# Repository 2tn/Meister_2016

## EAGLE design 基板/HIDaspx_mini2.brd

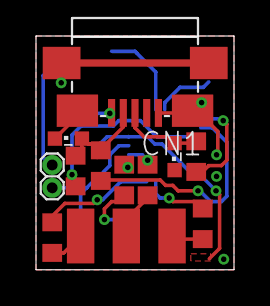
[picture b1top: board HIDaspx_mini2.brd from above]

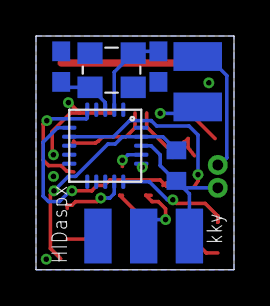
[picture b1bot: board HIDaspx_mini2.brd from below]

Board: 2 copper layers, 11.0 x 13.0 mm, 18 parts (6 on the bottom side), 20 nets.

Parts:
C4, C5: 22p; C0603
CN1: ZX62R-B-5P; MICRO-B
JP1: 1X02/HALF
LED1, LED2: BLUE; SML0603
PSW: 100m; C3225
R2: 2.2k; R0603
R3, R4: 75; R0603
R5: 10k; R0603
R6, R7, R8, R9: 100; R0603
U$1: TINY2313-*M*; MLF20
U$2: AVR-ISP-6-EDGE; 6PAD_ISP
X1: FA238V; V66RA

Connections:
GND: C4.2, C5.2, CN1.5, CN1.CASE@1, CN1.CASE@2, CN1.CASE@3, CN1.CASE@4, LED1.C, LED2.C, U$1.P$8, U$2.GND, X1.P2GND, X1.P4GND
MISO: R7.1, U$1.P$15
MOSI: R6.2, U$1.P$16
unnamed: C5.1, U$1.P$2, X1.P1X1
unnamed: JP1.2, PSW.1
unnamed: C4.1, U$1.P$3, X1.P3X2
unnamed: CN1.1, PSW.2
unnamed: CN1.2, LED2.A, R2.2, R3.2
unnamed: CN1.3, LED1.A, R4.2
unnamed: R2.1, U$1.P$7
unnamed: R3.1, U$1.P$6
unnamed: R4.1, U$1.P$5
unnamed: R5.2, U$1.P$19
unnamed: R8.2, U$2.SCK
unnamed: R7.2, U$2.MISO
unnamed: R9.2, U$2.RST
unnamed: R6.1, U$2.MOSI
RST: R9.1, U$1.P$14
SCK: R8.1, U$1.P$17
VCC: JP1.1, R5.1, U$1.P$18, U$2.VCC

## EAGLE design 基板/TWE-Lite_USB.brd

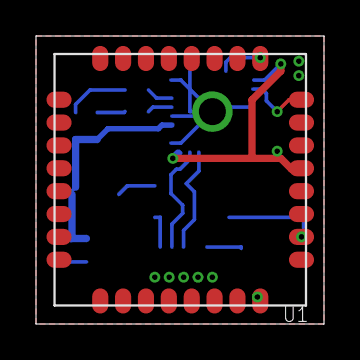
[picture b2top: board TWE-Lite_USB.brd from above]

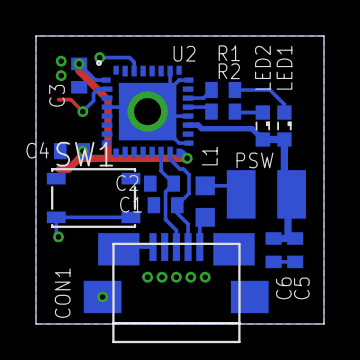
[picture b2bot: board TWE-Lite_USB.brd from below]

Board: 2 copper layers, 16.0 x 16.0 mm, 16 parts (15 on the bottom side), 14 nets.

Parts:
C1, C2, C3, C4, C5, C6: 0402
CON1: ZX62R-B-5P; MICRO-B
L1: C0603K
LED1, LED2: SML0603
PSW: 100m; C3225
R1, R2: R0402
SW1: SKRPACE010
U1: TWE-LITE_SMD; LITE
U2: FT232RQ; QFN32

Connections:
+3V3: C3.1, C4.1, U1.5, U2.1, U2.16
+5V: C5.1, C6.1, LED1.A, LED2.A, PSW.1, U2.19
GND: C1.2, C2.2, C3.2, C4.2, C5.2, C6.2, CON1.5, CON1.CASE@1, CON1.CASE@2, CON1.CASE@3, CON1.CASE@4, SW1.1, SW1.2, U1.20, U1.28, U1.30, U1.31, U1.32, U2.4, U2.17, U2.20, U2.24, U2.26, U2.PAD
unnamed: C1.1, CON1.2, U2.15
unnamed: C2.1, CON1.3, U2.14
unnamed: CON1.1, L1.2
unnamed: LED1.C, R1.2
unnamed: U1.9, U2.30
unnamed: U1.8, U2.2
unnamed: SW1.3, SW1.4, U1.2
unnamed: L1.1, PSW.2
unnamed: LED2.C, R2.2
unnamed: R1.1, U2.22
unnamed: R2.1, U2.21

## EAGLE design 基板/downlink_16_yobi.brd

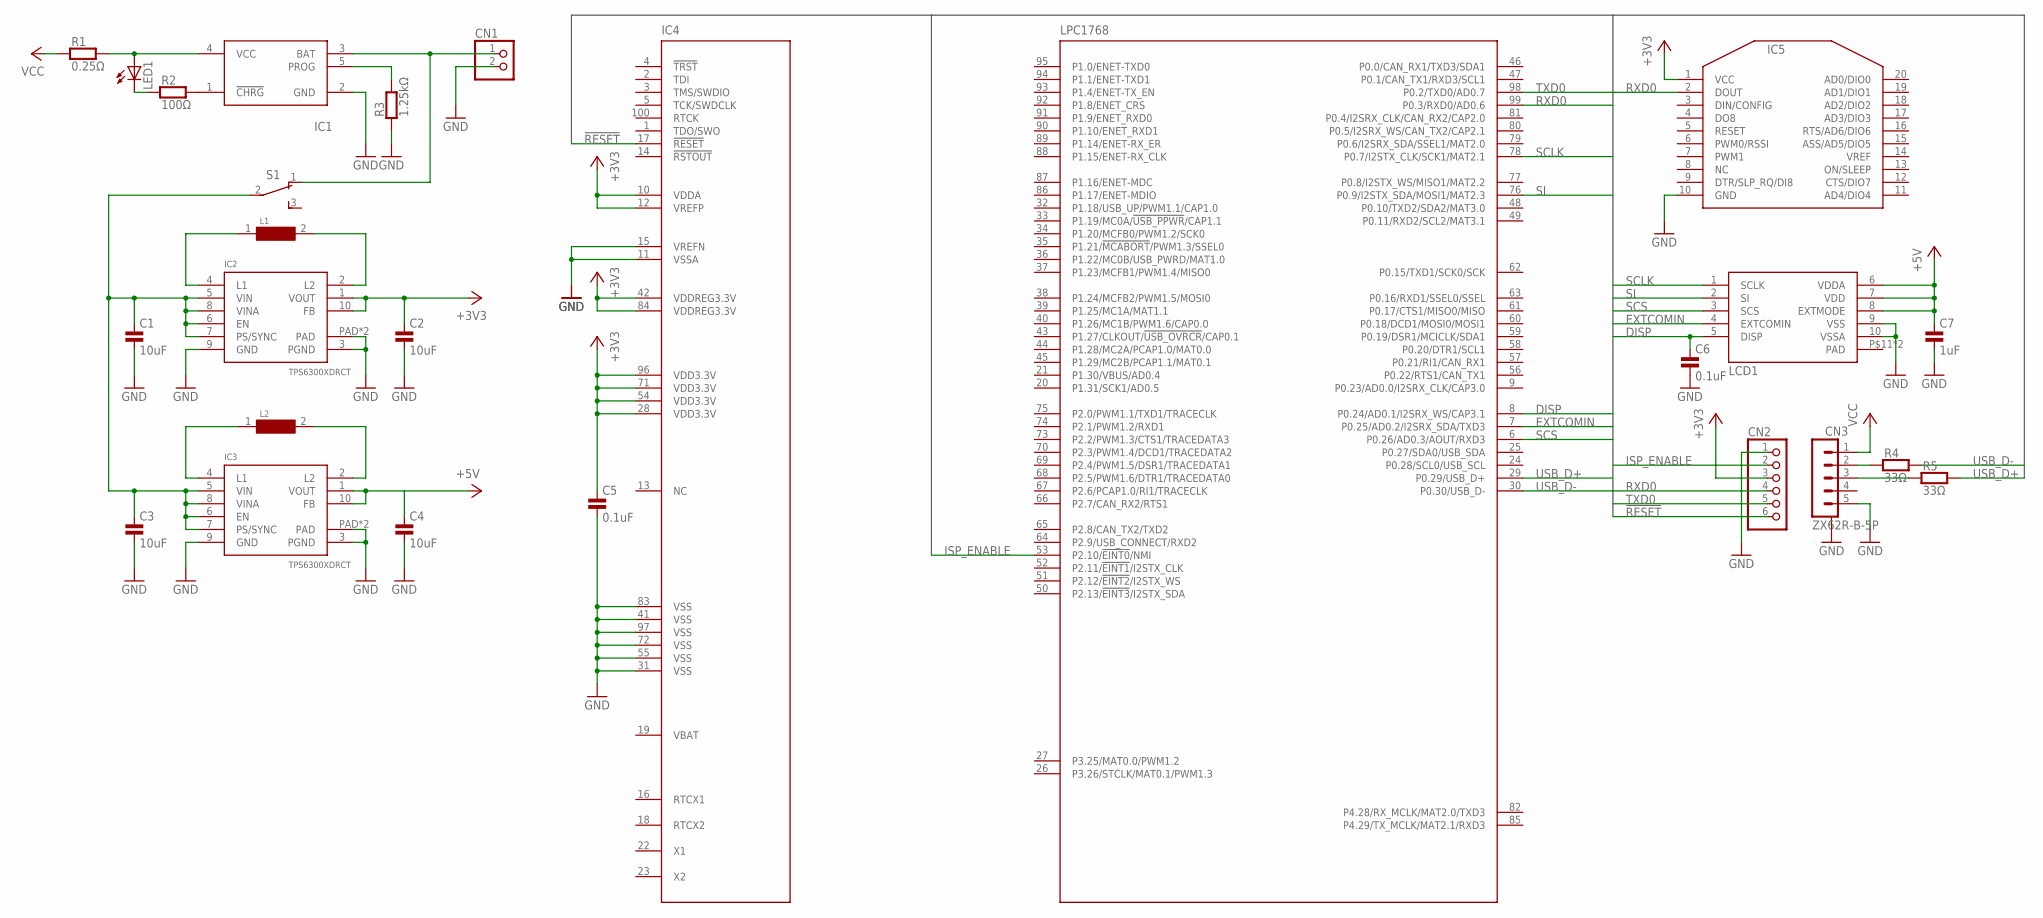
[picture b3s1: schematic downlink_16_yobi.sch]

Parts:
C1, C2, C3, C4: 10uF; 0603
C5, C6: 0.1uF; 0603
C7: 1uF; 0603
CN1: PINHD-1X2; 1X02
CN2: PINHD-1X6/90; 1X06/90
CN3: ZX62R-B-5P; MICRO-B
IC1: LTC4054; TSOT23-5
IC2, IC3: TPS6300XDRCT; S-PVSON-N10
IC4: LPC1768; LQFP100
IC5: XBEE-PRO2MM; XBEE-ZB
L1, L2: VLF4012ST
LCD1: LS027B4DH01SMD; FH12-10S-0.5SH
LED1: LEDSML0603; SML0603
R1: 0.25Ω; 0603
R2: 100Ω; 0603
R3: 1.25kΩ; 0603
R4, R5: 33Ω; 0603
S1: SS-12D00

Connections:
!RESET!: CN2.6, IC4.17 (!RESET!)
+3V3: C2.1, C5.1, CN2.3, IC2.1 (VOUT), IC2.10 (FB), IC4.10 (VDDA), IC4.12 (VREFP), IC4.28 (VDD3.3V), IC4.42 (VDDREG3.3V), IC4.54 (VDD3.3V), IC4.71 (VDD3.3V), IC4.84 (VDDREG3.3V), IC4.96 (VDD3.3V), IC5.1 (VCC)
+5V: C4.1, C7.1, IC3.1 (VOUT), IC3.10 (FB), LCD1.6 (VDDA), LCD1.7 (VDD), LCD1.8 (EXTMODE)
DISP: C6.1, IC4.8 (P0.24/AD0.1/I2SRX_WS/CAP3.1), LCD1.5 (DISP)
EXTCOMIN: IC4.7 (P0.25/AD0.2/I2SRX_SDA/TXD3), LCD1.4 (EXTCOMIN)
GND: C1.2, C2.2, C3.2, C4.2, C5.2, C6.2, C7.2, CN1.2, CN2.1, CN3.5 (1.VBUS), CN3.CASE@1, CN3.CASE@2, CN3.CASE@3, CN3.CASE@4, IC1.2 (GND), IC2.3 (PGND), IC2.9 (GND), IC2.PAD, IC2.PAD@1 (PAD), IC3.3 (PGND), IC3.9 (GND), IC3.PAD, IC3.PAD@1 (PAD), IC4.11 (VSSA), IC4.15 (VREFN), IC4.31 (VSS), IC4.41 (VSS), IC4.55 (VSS), IC4.72 (VSS), IC4.83 (VSS), IC4.97 (VSS), IC5.10 (GND), LCD1.9 (VSS), LCD1.10 (VSSA), R3.1
ISP_ENABLE: CN2.2, IC4.53 (P2.10/!EINT0!/NMI)
unnamed: CN3.2 (4.ID), R4.1
unnamed: CN3.3 (3.D+), R5.1
unnamed: IC1.5 (PROG), R3.2
unnamed: IC1.4 (VCC), LED1.A, R1.2
unnamed: CN1.1, IC1.3 (BAT), S1.1 (O)
unnamed: IC1.1 (!CHRG!), R2.2
unnamed: LED1.C, R2.1
unnamed: IC2.4 (L1), L1.1
unnamed: IC2.2 (L2), L1.2
unnamed: IC3.4 (L1), L2.1
unnamed: IC3.2 (L2), L2.2
unnamed: C1.1, C3.1, IC2.5 (VIN), IC2.6 (EN), IC2.7 (PS/SYNC), IC2.8 (VINA), IC3.5 (VIN), IC3.6 (EN), IC3.7 (PS/SYNC), IC3.8 (VINA), S1.2
RXD0: CN2.4, IC4.99 (P0.3/RXD0/AD0.6), IC5.2 (DOUT)
SCLK: IC4.78 (P0.7/I2STX_CLK/SCK1/MAT2.1), LCD1.1 (SCLK)
SCS: IC4.6 (P0.26/AD0.3/AOUT/RXD3), LCD1.3 (SCS)
SI: IC4.76 (P0.9/I2STX_SDA/MOSI1/MAT2.3), LCD1.2 (SI)
TXD0: CN2.5, IC4.98 (P0.2/TXD0/AD0.7)
USB_D+: IC4.29 (P0.29/USB_D+), R5.2
USB_D-: IC4.30 (P0.30/USB_D-), R4.2
VCC: CN3.1 (5.GND), R1.1

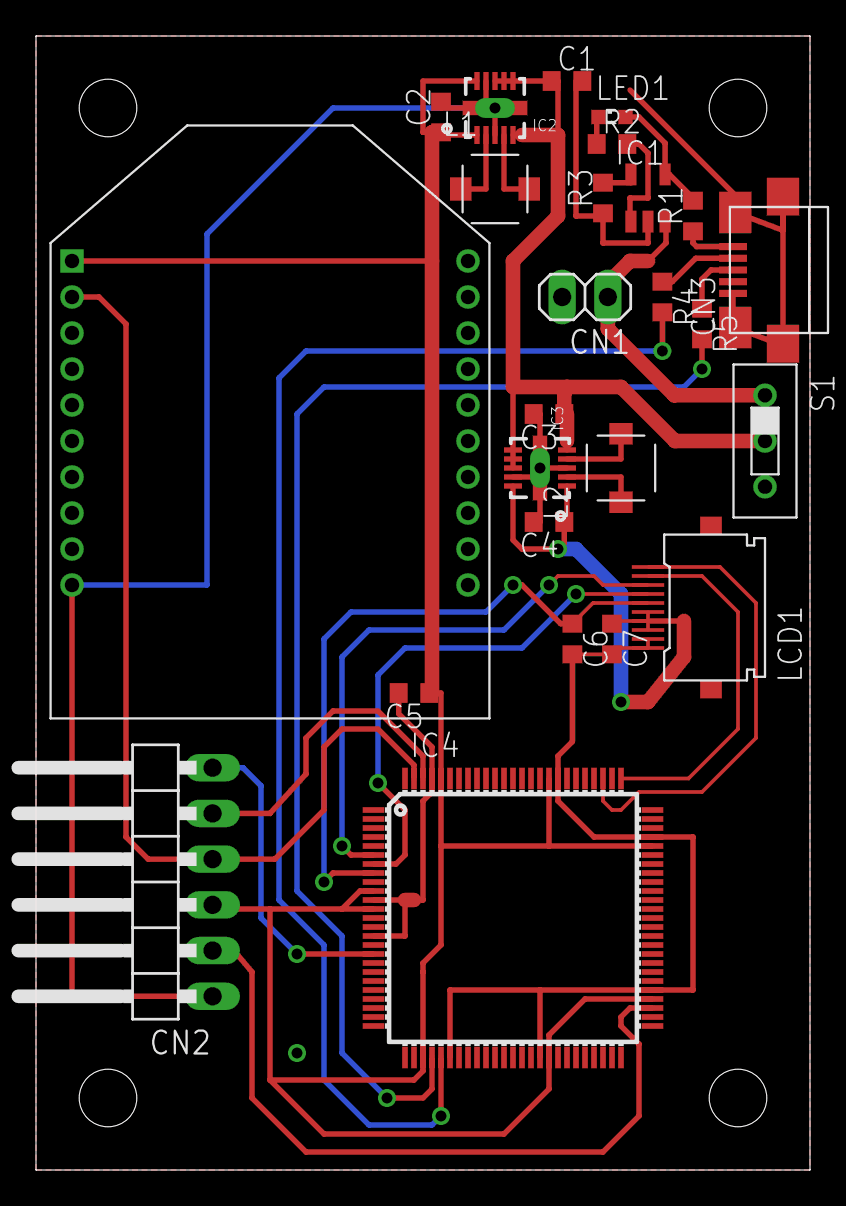
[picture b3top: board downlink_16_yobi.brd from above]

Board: 2 copper layers, 43.0 x 63.0 mm, 25 parts (0 on the bottom side), 27 nets.

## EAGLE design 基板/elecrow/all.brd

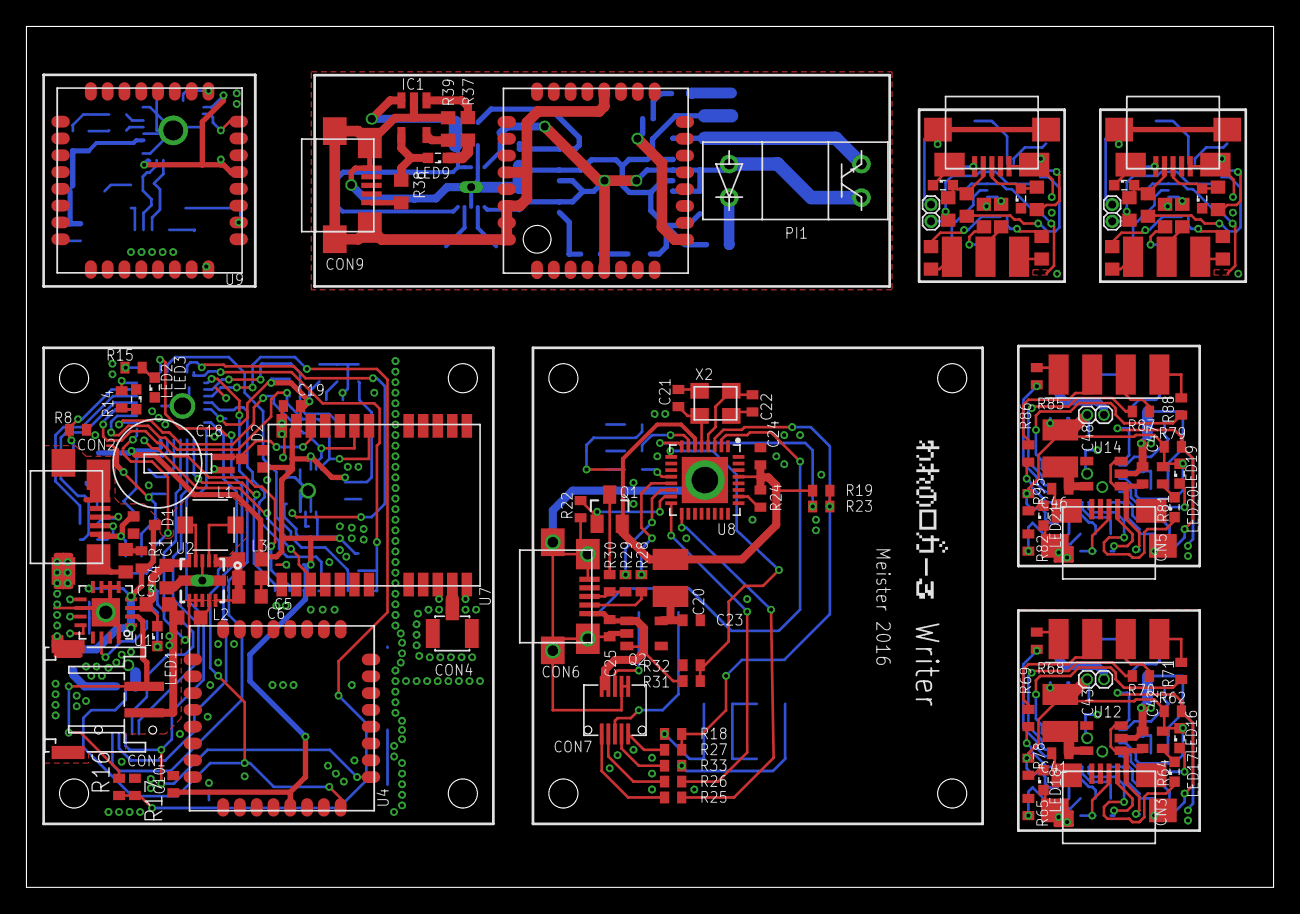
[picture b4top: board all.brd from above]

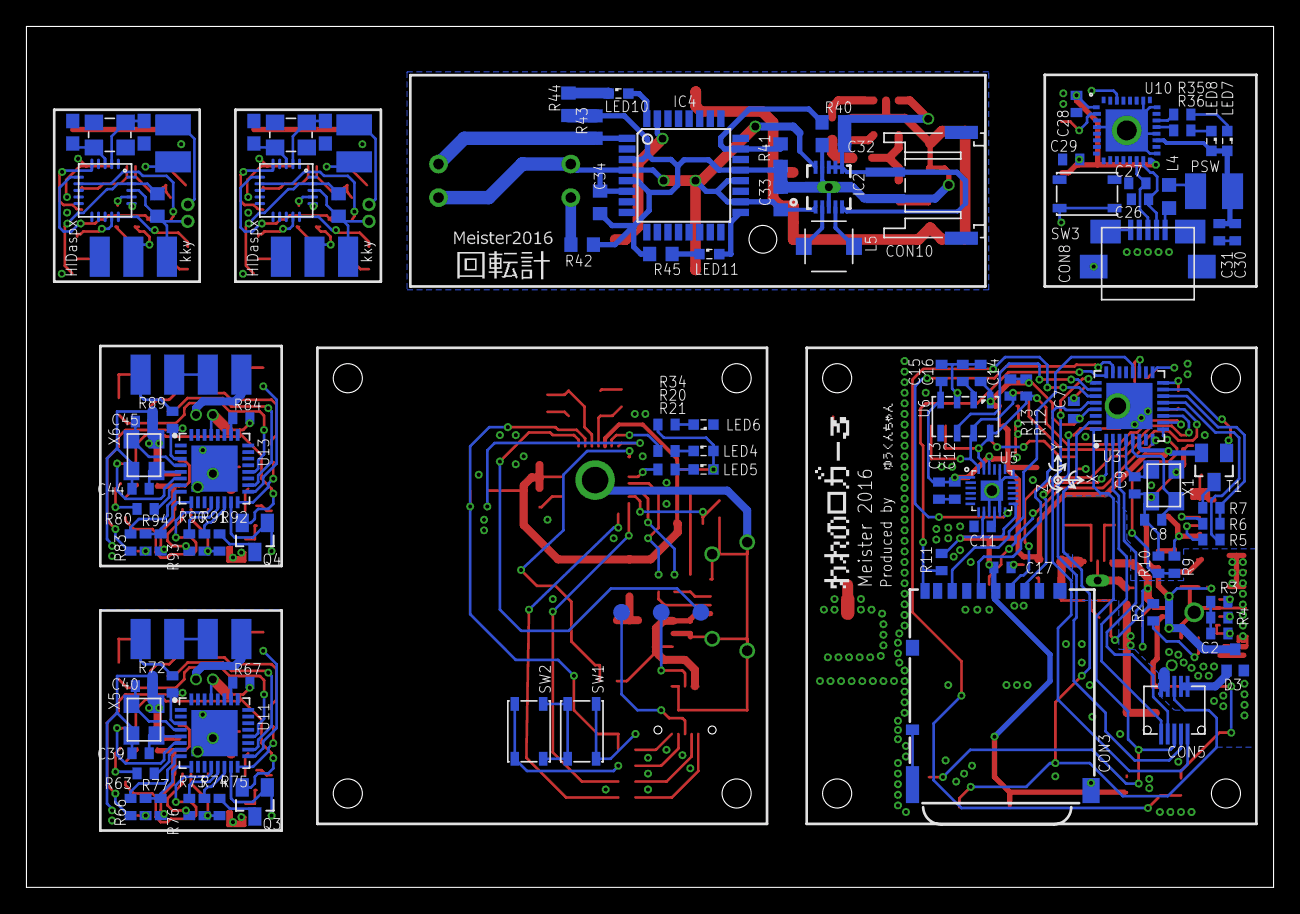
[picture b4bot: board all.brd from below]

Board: 2 copper layers, 94.3 x 65.1 mm, 236 parts (113 on the bottom side), 217 nets.

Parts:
C1, C3, C4, C5, C6, C32, C33: 10u; 0603
C2: 0.2u; 0402
C7, C10, C11, C12, C14, C16, C17, C19: 0.1u; 0402
C8, C9, C26, C27, C28, C29, C30, C31: 0402
C13: 10n; 0402
C15: 10u; 0402
C18: DCK-3R3E224-E
C20, C43, C48: PSW; C3225
C21, C22, C39, C40, C44, C45: 8P; C0402
C23, C25, C41, C42, C46, C47: 1u; C0402
C24: 0.1u; C0402
C34: 0.1u; 0603
C35, C36, C37, C38: 22p; C0603
CN1, CN2, CN3, CN5: ZX62R-B-5P; MICRO-B
CN4, CN6: 2X4SMD
CON1, CON10: JST-PH2
CON2, CON6, CON8, CON9: ZX62R-B-5P; MICRO-B
CON3: DM3AT-SF-PEJM5SMD; DM3AT-SF-PEJM5
CON4: U.FL; U.FL-R-SMT-1
CON5: DF12#-10DS; DF12A-10DS
CON7: DF12#-10DP; DF12D-10DP
D1, D2, D3: RB461F; UMD3
IC1: TSOT23-5
IC2: S-PVSON-N10
IC3: LITESMD; LITE
IC4: ATMEGA48/88/168-AU; TQFP32-08
JP1, JP2: 1X02/HALF
JP3, JP4: 1X02/HARF
L1, L5: 2.2u; VLF4012ST
L2, L3: BLM; C0603K
L4: C0603K
LED1, LED2, LED3, LED4, LED5, LED6, LED7, LED8, LED9, LED10, LED11, LED16, LED17, LED18, LED19, LED20, LED21: SML0603
LED12, LED13, LED14, LED15: BLUE; SML0603
PI1: RPI-574
PSW, PSW1, PSW2: 100m; C3225
Q1, Q3, Q4: PDTA114ET; SOT23
Q2: MIC550X; SOT23_5PIN
R1: 1; 0402
R2, R14, R15: 100; 0402
R3: 105k; 0402
R4: 124k; 0402
R5, R6: 33; 0402
R7: 1.5k; 0402
R8, R10: 10k; 0402
R9: 5.6k; 0402
R11, R12, R13: 4.7k; 0402
R16: 3.3k; 0402
R17: 2.2k; 0402
R18, R23, R25, R26, R27, R33, R66, R68, R69, R70, R71, R72, R83, R85, R86, R87, R88, R89: 270; R0402
R19, R22, R24, R32, R62, R65, R67, R77, R79, R82, R84, R94: 10k; R0402
R20, R21, R30, R63, R64, R75, R80, R81, R92: 1.5k; R0402
R28, R29, R73, R74, R90, R91: 33; R0402
R31, R76, R93: 5.6k; R0402
R34, R78, R95: 750; R0402
R35, R36: R0402
R37: 100; 0603
R38: 0.25; 0603
R39: 3.2k; 0603
R40: 3.3k; 0603
R41: 2.2k; 0603
R42, R44, R45: 200; 0603
R43: 1.0M; 0603
R46, R54: 2.2k; R0603
R47, R48, R55, R56: 75; R0603
R49, R57: 10k; R0603
R50, R51, R52, R53, R58, R59, R60, R61: 100; R0603
SW1, SW2, SW3: SKRPACE010
T1: PDTA114ET; SOT23
U1: LTC4055; QFN16
U2: TPS6300XDRCT; S-PVSON-N10
U3, U8, U11, U13: LPC11U35FHI33/501; SOT617-3
U4, U9: TWE-LITE_SMD; LITE
U5: MPU-9250
U6: MPL3115A2
U7: NEO-7M
U10: FT232RQ; QFN32
U12, U14: MIC550X; SOT23_5PIN
U$1: DIRECTION
U$2, U$3, U$4: TESTPAD
U$5, U$7: TINY2313-*M*; MLF20
U$6, U$8: AVR-ISP-6-EDGE; 6PAD_ISP
X1, X2, X3, X4, X5, X6: FA238V; V66RA

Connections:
!RESET!: CON5.10, U3.2
!USB_CONNECT!: R8.2, T1.1, U3.15
!USB_CONNECT!1: Q1.1, R22.2, U8.15
!USB_CONNECT!2: Q3.1, R65.2, U11.15
!USB_CONNECT!3: Q4.1, R82.2, U13.15
+3V1: C28.1, C29.1, U9.5, U10.1, U10.16
+3V2: C33.1, C34.1, IC2.1, IC2.10, IC3.5, IC4.4, IC4.6, IC4.18, IC4.20, PI1.DA, PI1.TC
+3V3: C7.1, C10.1, C12.1, C13.1, C14.1, C15.1, C17.1, C19.1, CON3.4, D2.2, L3.1, R11.2, R12.2, R13.2, T1.2, U3.6, U3.29, U4.5, U5.1, U5.8, U5.13, U5.22, U6.1, U6.4, U7.23
+5V: D1.3, D3.3, R1.2, U1.1, U1.4, U1.8
+5V1: C30.1, C31.1, LED7.A, LED8.A, PSW.1, U10.19
AD7: R16.1, R17.2, U3.27
BOOT: CON7.8, R33.2
D+USB: CON6.3, R29.2, R30.1
D+USB1: CN3.3, R74.2, R75.1
D+USB2: CN5.3, R91.2, R92.1
D-USB: CON6.2, R28.2
D-USB1: CN3.2, R73.2
D-USB2: CN5.2, R90.2
GND: C5.2, C6.2, C7.2, C8.2, C9.2, C10.2, C11.2, C12.2, C13.2, C14.2, C15.2, C16.2, C17.2, C18.1, C19.2, CON3.6, CON3.10, CON3.P$10, CON3.P$11, CON3.P$12, CON3.P$14, CON4.1, CON4.2, L2.2, LED2.C, LED3.C, R8.1, R10.1, R17.1, U2.9, U3.33, U4.20, U4.28, U4.30, U4.31, U4.32, U5.9, U5.11, U5.18, U5.20, U5.PAD, U6.3, U7.10, U7.12, U7.13, U7.24, X1.P2GND, X1.P4GND
GND1: C21.2, C22.2, C23.2, C24.2, C25.2, CON6.5, CON6.CASE@1, CON6.CASE@2, CON6.CASE@3, CON6.CASE@4, CON7.7, CON7.9, LED6.C, Q2.2, R22.1, R32.1, SW1.1, SW1.2, SW2.1, SW2.2, U8.33, X2.P2GND, X2.P4GND
GND2: C26.2, C27.2, C28.2, C29.2, C30.2, C31.2, CON8.5, CON8.CASE@1, CON8.CASE@2, CON8.CASE@3, CON8.CASE@4, SW3.1, SW3.2, U9.20, U9.28, U9.30, U9.31, U9.32, U10.4, U10.17, U10.20, U10.24, U10.26, U10.PAD
GND3: C32.2, C33.2, C34.2, CON9.5, CON9.CASE@1, CON9.CASE@2, CON9.CASE@3, CON9.CASE@4, CON10.1, IC1.2, IC2.3, IC2.9, IC2.PAD, IC2.PAD@1, IC3.20, IC3.28, IC3.30, IC3.31, IC3.32, IC4.3, IC4.5, IC4.21, R39.1, R41.1, R42.1, R43.2, R44.1, R45.1
GND4: C35.2, C36.2, CN1.5, CN1.CASE@1, CN1.CASE@2, CN1.CASE@3, CN1.CASE@4, LED12.C, LED13.C, U$5.P$8, U$6.GND, X3.P2GND, X3.P4GND
GND5: C37.2, C38.2, CN2.5, CN2.CASE@1, CN2.CASE@2, CN2.CASE@3, CN2.CASE@4, LED14.C, LED15.C, U$7.P$8, U$8.GND, X4.P2GND, X4.P4GND
GND6: C39.2, C40.2, C41.2, C42.2, CN3.5, CN3.CASE@1, CN3.CASE@2, CN3.CASE@3, CN3.CASE@4, CN4.3, CN4.5, LED18.C, R65.1, R77.1, U11.33, U12.2, X5.P2GND, X5.P4GND
GND7: C44.2, C45.2, C46.2, C47.2, CN5.5, CN5.CASE@1, CN5.CASE@2, CN5.CASE@3, CN5.CASE@4, CN6.3, CN6.5, LED21.C, R82.1, R94.1, U13.33, U14.2, X6.P2GND, X6.P4GND
MISO1: CON3.7, U3.20
MISO2: R59.1, U$7.P$15
MISO3: R51.1, U$5.P$15
MOSI1: CON3.3, U3.12
MOSI2: R58.2, U$7.P$16
MOSI3: R50.2, U$5.P$16
unnamed: C8.1, U3.5, X1.P1X1
unnamed: CON2.2, R5.1
unnamed: C9.1, U3.4, X1.P3X2
unnamed: CON2.3, R6.1
unnamed: R7.2, T1.3
unnamed: LED3.A, R15.1
unnamed: CON4.3, U7.11
unnamed: C16.1, U6.2
unnamed: L1.2, U2.2
unnamed: C11.1, U5.10
unnamed: L1.1, U2.4
unnamed: LED2.A, R14.1
unnamed: C21.1, U8.5, X2.P1X1
unnamed: C22.1, U8.4, X2.P3X2
unnamed: R29.1, U8.14
unnamed: C1.1, R1.1
unnamed: C5.1, C6.1, L3.2, U2.1, U2.10
unnamed: CON5.1, CON5.3, D3.2
unnamed: R3.2, U1.9
unnamed: R4.2, U1.11
unnamed: C2.1, U1.12
unnamed: R2.1, U1.14
unnamed: LED1.C, R2.2
unnamed: C3.1, C4.1, LED1.A, U1.3, U2.5, U2.6, U2.7, U2.8
unnamed: CON1.1, R16.2, U1.2
unnamed: C18.2, D2.3, U7.22
unnamed: R28.1, U8.13
unnamed: Q1.3, R30.2
unnamed: CON7.2, R25.1
unnamed: CON7.4, R26.1
unnamed: LED6.A, R34.2
unnamed: LED4.C, R20.1
unnamed: C20.2, C23.1, Q2.5
unnamed: CON7.10, R27.1
unnamed: R18.1, SW1.3, SW1.4
unnamed: R33.1, SW2.3, SW2.4
unnamed: U8.2, U$4.P$1
unnamed: LED5.C, R21.1
unnamed: C26.1, CON8.2, U10.15
unnamed: C27.1, CON8.3, U10.14
unnamed: CON8.1, L4.2
unnamed: U9.9, U10.30
unnamed: U9.8, U10.2
unnamed: L4.1, PSW.2
unnamed: LED7.C, R35.2
unnamed: LED8.C, R36.2
unnamed: R35.1, U10.22
unnamed: R36.1, U10.21
unnamed: SW3.3, SW3.4, U9.2
unnamed: IC1.4, LED9.A, R38.2
unnamed: IC1.1, R37.2
unnamed: LED9.C, R37.1
unnamed: IC2.4, L5.1
unnamed: IC2.2, L5.2
unnamed: CON9.1, R38.1
unnamed: IC1.5, R39.2
unnamed: IC4.23, R40.1, R41.2
unnamed: IC4.1, PI1.TE, R43.1
unnamed: PI1.DC, R42.2
unnamed: IC4.17, LED11.A
unnamed: LED11.C, R45.2
unnamed: IC4.32, LED10.A
unnamed: LED10.C, R44.2
unnamed: C36.1, U$5.P$2, X3.P1X1
unnamed: C35.1, U$5.P$3, X3.P3X2
unnamed: CN1.1, PSW1.2
unnamed: CN1.2, LED13.A, R46.2, R47.2
unnamed: CN1.3, LED12.A, R48.2
unnamed: R46.1, U$5.P$7
unnamed: R47.1, U$5.P$6
unnamed: R48.1, U$5.P$5
unnamed: R49.2, U$5.P$19
unnamed: R52.2, U$6.SCK
unnamed: R51.2, U$6.MISO
unnamed: R53.2, U$6.RST
unnamed: R50.1, U$6.MOSI
unnamed: JP1.2, PSW1.1
unnamed: C38.1, U$7.P$2, X4.P1X1
unnamed: C37.1, U$7.P$3, X4.P3X2
unnamed: CN2.1, PSW2.2
unnamed: CN2.2, LED15.A, R54.2, R55.2
unnamed: CN2.3, LED14.A, R56.2
unnamed: R54.1, U$7.P$7
unnamed: R55.1, U$7.P$6
unnamed: R56.1, U$7.P$5
unnamed: R57.2, U$7.P$19
unnamed: R60.2, U$8.SCK
unnamed: R59.2, U$8.MISO
unnamed: R61.2, U$8.RST
unnamed: R58.1, U$8.MOSI
unnamed: JP2.2, PSW2.1
unnamed: C39.1, U11.5, X5.P1X1
unnamed: C40.1, U11.4, X5.P3X2
unnamed: R74.1, U11.14
unnamed: R73.1, U11.13
unnamed: Q3.3, R75.2
unnamed: CN4.2, R68.1
unnamed: CN4.4, R69.1
unnamed: CN4.6, R70.1
unnamed: CN4.8, R71.1
unnamed: LED18.A, R78.2
unnamed: LED17.A, R64.2
unnamed: LED16.C, R63.1
unnamed: C41.1, C43.2, U12.5
unnamed: CN4.7, R72.1
unnamed: CN4.1, JP3.1
unnamed: C44.1, U13.5, X6.P1X1
unnamed: C45.1, U13.4, X6.P3X2
unnamed: R91.1, U13.14
unnamed: R90.1, U13.13
unnamed: Q4.3, R92.2
unnamed: CN6.2, R85.1
unnamed: CN6.4, R86.1
unnamed: CN6.6, R87.1
unnamed: CN6.8, R88.1
unnamed: LED21.A, R95.2
unnamed: LED20.A, R81.2
unnamed: LED19.C, R80.1
unnamed: C46.1, C48.2, U14.5
unnamed: CN6.7, R89.1
unnamed: CN6.1, JP4.1
PGND: C1.2, C2.2, C3.2, C4.2, CON1.2, CON1.PAD1, CON1.PAD2, CON2.5, CON2.CASE@1, CON2.CASE@2, CON2.CASE@3, CON2.CASE@4, CON5.7, CON5.9, L2.1, R3.1, R4.1, U1.5, U1.6, U1.7, U1.10, U1.16, U1.PAD, U2.3, U2.PAD, U2.PAD@1
PIO0_1: CON5.8, U3.3
PIO0_2: U3.8, U7.3
PIO0_3: R23.2, U8.8
PIO0_4: R24.1, U8.26
PIO0_5: R66.2, U11.8
PIO0_6: LED17.C, U11.12
PIO0_7: R14.2, U3.16
PIO0_8: R15.2, U3.17
PIO0_9: R67.1, U11.26
PIO0_10: R63.2, U11.7
PIO0_11: R83.2, U13.8
PIO0_12: LED20.C, U13.12
PIO0_13: U3.23, U5.12
PIO0_14: CON3.9, R11.1, U3.24
PIO0_15: R84.1, U13.26
PIO0_16: U3.26, U6.6
PIO0_17: R80.2, U13.7
PIO0_20: R20.2, U8.7
PIO0_21: R21.2, U8.12
PIO1_19: CON3.2, U3.1
RST1: R61.1, U$7.P$14
RST2: R53.1, U$5.P$14
RXD: CON5.5, U3.31, U4.8
RXD1: CON7.5, U$3.P$1
SCK1: CON3.5, U3.28
SCK2: R60.1, U$7.P$17
SCK3: R52.1, U$5.P$17
SCL: R12.1, U3.10, U5.23, U6.8, U7.19
SDA: R13.1, U3.11, U5.24, U6.7, U7.18
SWCLK: CON5.4, U3.19
SWDIO: CON5.2, U3.25
TARGET_!RESET!: R18.2, R19.2, R23.1, R27.2, U8.3
TARGET_!RESET!1: R62.2, R66.1, R72.2, U11.3
TARGET_!RESET!2: R79.2, R83.1, R89.2, U13.3
TARGET_SWCLK: R26.2, U8.16
TARGET_SWCLK1: R69.2, U11.16
TARGET_SWCLK2: R86.2, U13.16
TARGET_SWDIO: R25.2, U8.17
TARGET_SWDIO1: R68.2, U11.17
TARGET_SWDIO2: R85.2, U13.17
TARGET_SWO: R70.2, U11.18
TARGET_SWO1: R87.2, U13.18
TARGET_TDI: R71.2, U11.20
TARGET_TDI1: R88.2, U13.20
TXD: CON5.6, U3.32, U4.9
TXD1: CON7.6, U$2.P$1
U3: IC3.9, IC4.31
USB_D+: R6.2, R7.1, U3.14
USB_D-: R5.2, U3.13
USB_VBUS: R9.1, R10.2, U3.9
USB_VBUS1: R31.1, R32.2, U8.9
USB_VBUS2: R76.1, R77.2, U11.9
USB_VBUS3: R93.1, R94.2, U13.9
VBUS: CON2.1, D1.2, R9.2
VCC: C25.1, CON6.1, CON7.1, CON7.3, Q2.1, Q2.3, R31.2
VCC1: C32.1, CON10.2, IC1.3, IC2.5, IC2.6, IC2.7, IC2.8, R40.2
VCC2: JP1.1, R49.1, U$5.P$18, U$6.VCC
VCC3: JP2.1, R57.1, U$7.P$18, U$8.VCC
VCC4: C42.1, CN3.1, R76.2, U12.1, U12.3
VCC5: C47.1, CN5.1, R93.2, U14.1, U14.3
VDD: C20.1, C24.1, LED4.A, LED5.A, Q1.2, R19.1, R24.2, R34.1, U8.6, U8.29
VDD1: C43.1, JP3.2, LED16.A, Q3.2, R62.1, R64.1, R67.2, R78.1, U11.6, U11.29
VDD2: C48.1, JP4.2, LED19.A, Q4.2, R79.1, R81.1, R84.2, R95.1, U13.6, U13.29

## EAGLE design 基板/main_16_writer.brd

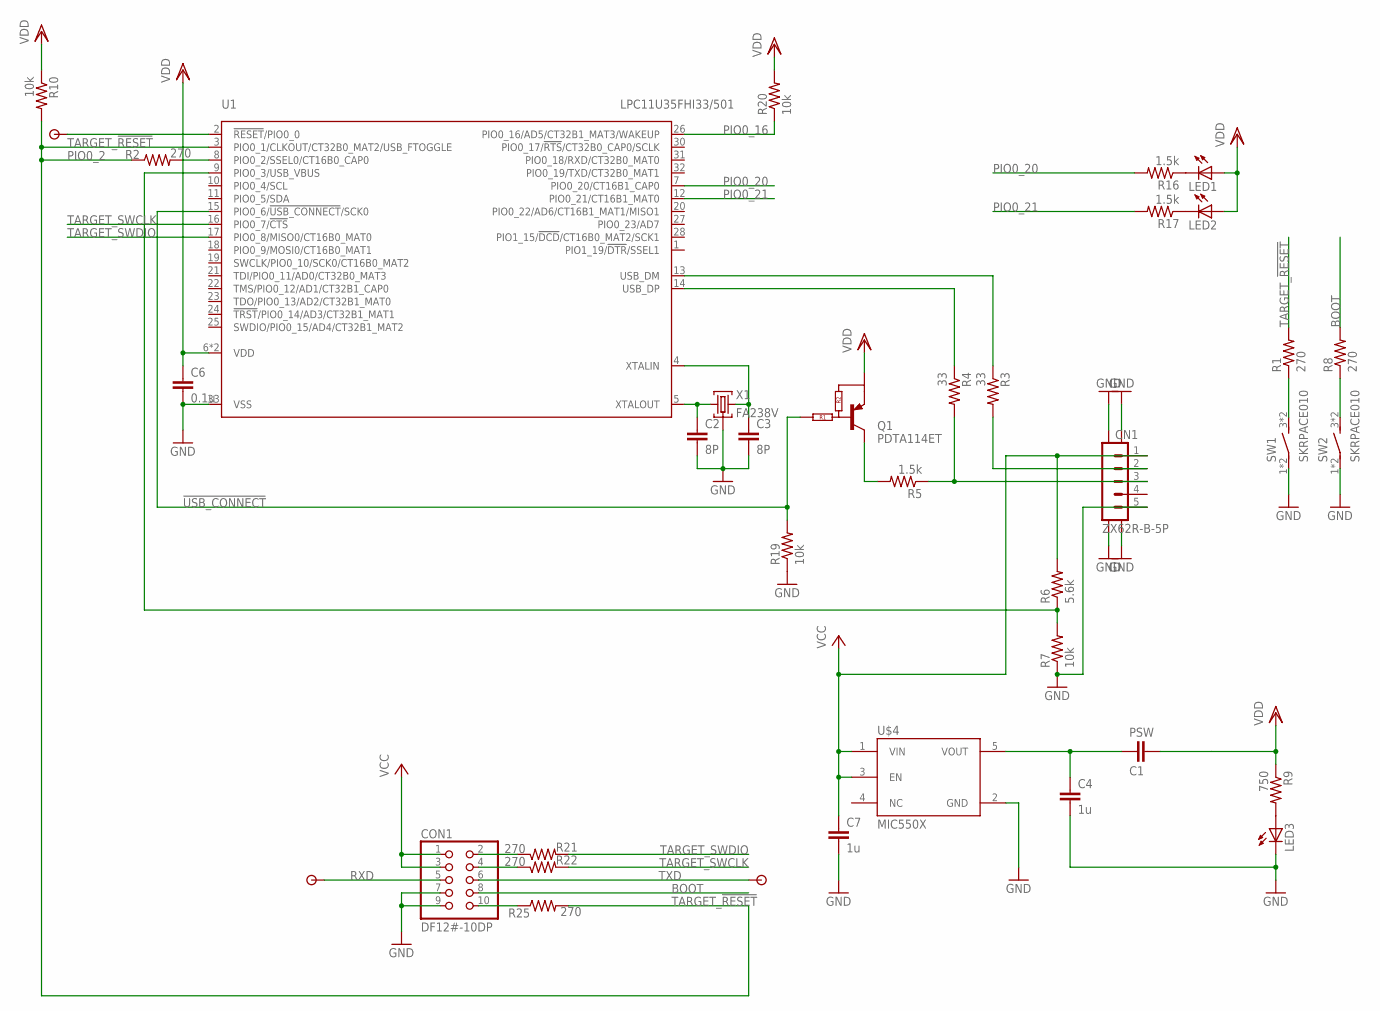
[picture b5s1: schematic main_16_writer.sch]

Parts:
C1: PSW; C3225
C2, C3: 8P; C0402
C4, C7: 1u; C0402
C6: 0.1u; C0402
CN1: ZX62R-B-5P; MICRO-B
CON1: DF12#-10DP; DF12D-10DP
LED1, LED2, LED3: LEDSML0603; SML0603
Q1: PDTA114ET; SOT23
R1, R2, R8, R21, R22, R25: 270; R0402
R3, R4: 33; R0402
R5, R16, R17: 1.5k; R0402
R6: 5.6k; R0402
R7, R10, R19, R20: 10k; R0402
R9: 750; R0402
SW1, SW2: SKRPACE010
U1: LPC11U35FHI33/501; SOT617-3
U$1, U$2, U$3: TESTPAD
U$4: MIC550X; SOT23_5PIN
X1: FA238V; V66RA

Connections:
!USB_CONNECT!: Q1.1 (INPUT), R19.2, U1.15 (PIO0_6/!USB_CONNECT!/SCK0)
BOOT: CON1.8, R8.2
D+USB: CN1.3 (3.D+), R4.2, R5.1
D-USB: CN1.2 (4.ID), R3.2
GND: C2.2, C3.2, C4.2, C6.2, C7.2, CN1.5 (1.VBUS), CN1.CASE@1 (1), CN1.CASE@2 (2), CN1.CASE@3 (3), CN1.CASE@4 (4), CON1.7, CON1.9, LED3.C, R7.1, R19.1, SW1.1, SW1.2, SW2.1, SW2.2, U1.33 (VSS), U$4.2 (GND), X1.P2GND (GND), X1.P4GND (GND)
unnamed: LED1.C, R16.1
unnamed: C2.1, U1.5 (XTALOUT), X1.P1X1 (X1)
unnamed: C3.1, U1.4 (XTALIN), X1.P3X2 (X2)
unnamed: C1.2, C4.1, U$4.5 (VOUT)
unnamed: R1.1, SW1.3 (S), SW1.4 (S)
unnamed: Q1.3 (C), R5.2
unnamed: R4.1, U1.14 (USB_DP)
unnamed: R3.1, U1.13 (USB_DM)
unnamed: CON1.10, R25.1
unnamed: LED2.C, R17.1
unnamed: R8.1, SW2.3 (S), SW2.4 (S)
unnamed: U1.2 (!RESET!/PIO0_0), U$3.P$1
unnamed: CON1.2, R21.1
unnamed: CON1.4, R22.1
unnamed: LED3.A, R9.2
PIO0_2: R2.2, U1.8 (PIO0_2/SSEL0/CT16B0_CAP0)
PIO0_16: R20.1, U1.26 (PIO0_16/AD5/CT32B1_MAT3/WAKEUP)
PIO0_20: R16.2, U1.7 (PIO0_20/CT16B1_CAP0)
PIO0_21: R17.2, U1.12 (PIO0_21/CT16B1_MAT0)
RXD: CON1.5, U$2.P$1
TARGET_!RESET!: R1.2, R2.1, R10.2, R25.2, U1.3 (PIO0_1/CLKOUT/CT32B0_MAT2/USB_FTOGGLE)
TARGET_SWCLK: R22.2, U1.16 (PIO0_7/!CTS!)
TARGET_SWDIO: R21.2, U1.17 (PIO0_8/MISO0/CT16B0_MAT0)
TXD: CON1.6, U$1.P$1
USB_VBUS: R6.1, R7.2, U1.9 (PIO0_3/USB_VBUS)
VCC: C7.1, CN1.1 (5.GND), CON1.1, CON1.3, R6.2, U$4.1 (VIN), U$4.3 (EN)
VDD: C1.1, C6.1, LED1.A, LED2.A, Q1.2 (E), R9.1, R10.1, R20.2, U1.6 (VDD), U1.29 (VDD)

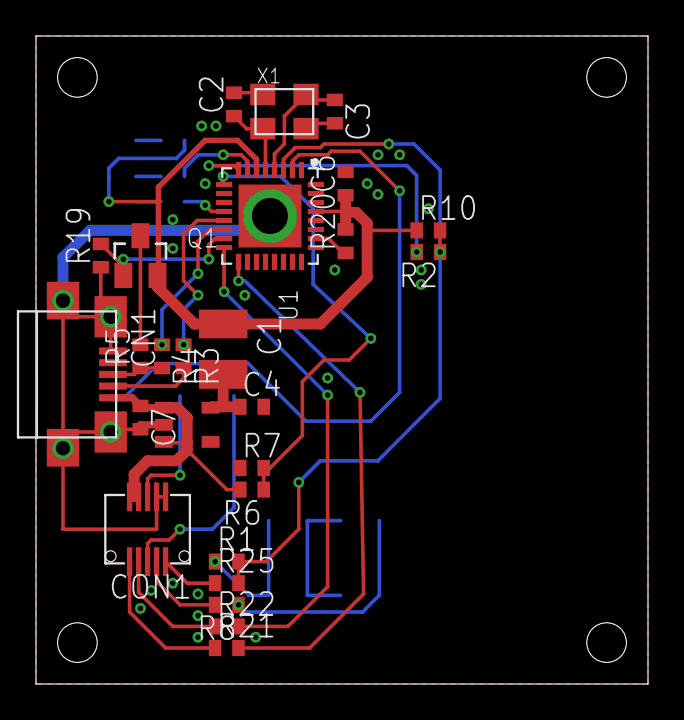
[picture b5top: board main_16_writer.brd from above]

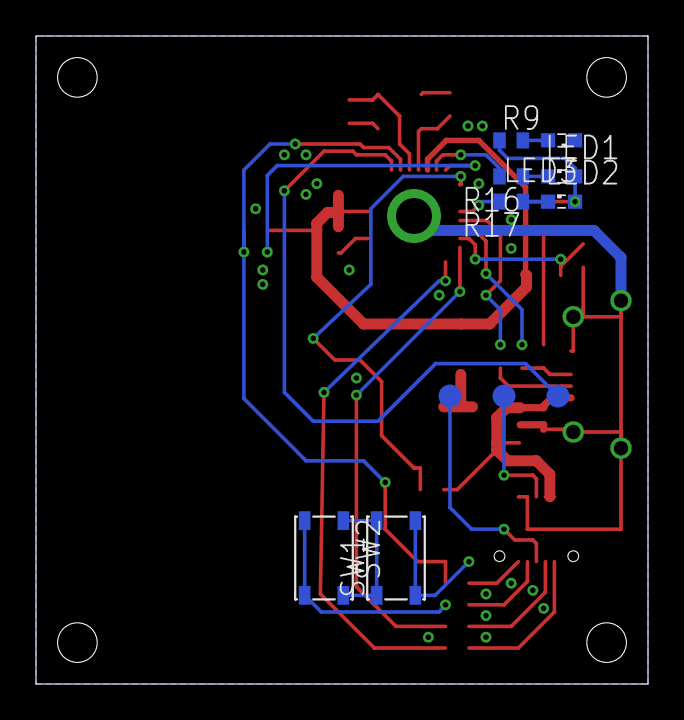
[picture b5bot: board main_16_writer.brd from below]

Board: 2 copper layers, 34.0 x 36.0 mm, 37 parts (12 on the bottom side), 32 nets.

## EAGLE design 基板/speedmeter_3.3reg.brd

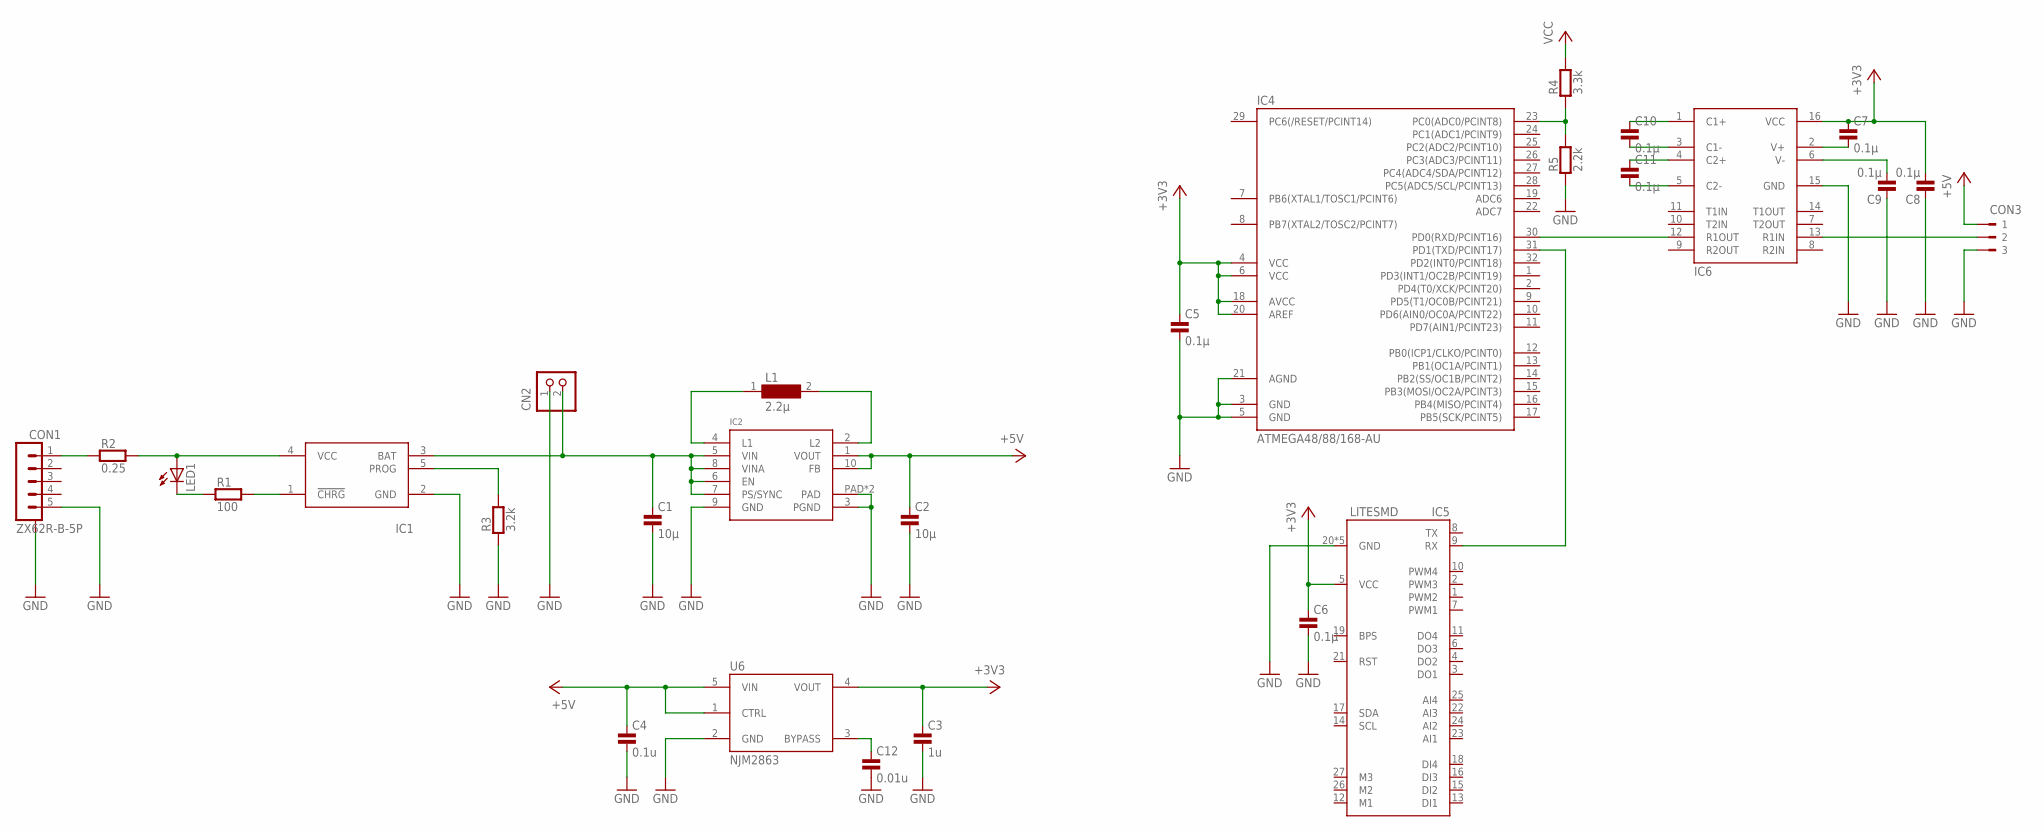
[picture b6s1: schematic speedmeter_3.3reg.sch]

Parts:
C1, C2: 10μ; 0603@1
C3: 1u; 0603@1
C4: 0.1u; 0603@1
C5, C6: 0.1μ; 0603@1
C7, C8, C9, C10, C11: 0.1μ; 0603
C12: 0.01u; 0603@1
CN2: S2B-PH-K-S
CON1: ZX62R-B-5P; MICRO-B
CON3: 180-3
IC1: LTC4054; TSOT23-5
IC2: TPS6300XDRCT; S-PVSON-N10
IC4: ATMEGA48/88/168-AU; TQFP32-08
IC5: LITESMD; LITE
IC6: ADM3202ARN; SOP16
L1: 2.2μ; VLF4012ST
LED1: LEDSML0603; SML0603
R1: 100; 0603
R2: 0.25; 0603
R3: 3.2k; 0603
R4: 3.3k; 0603
R5: 2.2k; 0603
U6: NJM2863; SOT23_5PIN

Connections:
+3V3: C3.1, C5.1, C6.1, C7.1, C8.2, IC4.4 (VCC), IC4.6 (VCC), IC4.18 (AVCC), IC4.20 (AREF), IC5.5 (VCC), IC6.16 (VCC), U6.4 (VOUT)
+5V: C2.1, C4.1, CON3.1, IC2.1 (VOUT), IC2.10 (FB), U6.1 (CTRL), U6.5 (VIN)
GND: C1.2, C2.2, C3.2, C4.2, C5.2, C6.2, C8.1, C9.1, C12.2, CN2.1, CON1.5 (1.VBUS), CON1.CASE@1, CON1.CASE@2, CON1.CASE@3, CON1.CASE@4, CON3.3, IC1.2 (GND), IC2.3 (PGND), IC2.9 (GND), IC2.PAD, IC2.PAD@1 (PAD), IC4.3 (GND), IC4.5 (GND), IC4.21 (AGND), IC5.20 (GND), IC5.28 (GND), IC5.30 (GND), IC5.31 (GND), IC5.32 (GND), IC6.15 (GND), R3.1, R5.1, U6.2 (GND)
unnamed: CON1.1 (5.GND), R2.1
unnamed: IC1.4 (VCC), LED1.A, R2.2
unnamed: LED1.C, R1.1
unnamed: IC1.1 (!CHRG!), R1.2
unnamed: IC1.5 (PROG), R3.2
unnamed: IC2.4 (L1), L1.1
unnamed: IC2.2 (L2), L1.2
unnamed: CON3.2, IC6.13 (R1IN)
unnamed: C12.1, U6.3 (BYPASS)
unnamed: IC4.23 (PC0(ADC0/PCINT8)), R4.1, R5.2
unnamed: IC4.31 (PD1(TXD/PCINT17)), IC5.9 (RX)
unnamed: C7.2, IC6.2 (V+)
unnamed: C9.2, IC6.6 (V-)
unnamed: C10.1, IC6.1 (C1+)
unnamed: C10.2, IC6.3 (C1-)
unnamed: C11.1, IC6.4 (C2+)
unnamed: C11.2, IC6.5 (C2-)
unnamed: IC4.30 (PD0(RXD/PCINT16)), IC6.12 (R1OUT)
VCC: C1.1, CN2.2, IC1.3 (BAT), IC2.5 (VIN), IC2.6 (EN), IC2.7 (PS/SYNC), IC2.8 (VINA), R4.2

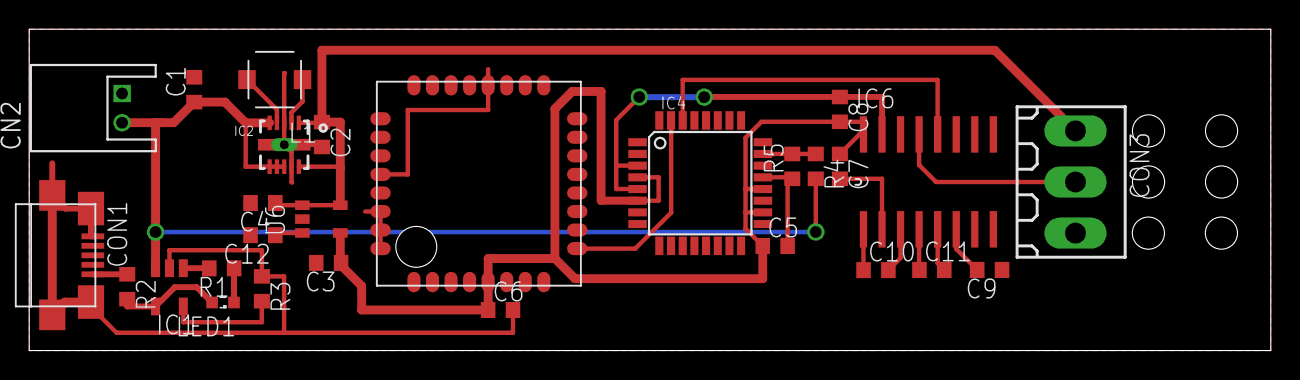
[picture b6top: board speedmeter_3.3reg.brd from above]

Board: 2 copper layers, 85.0 x 22.0 mm, 28 parts (0 on the bottom side), 22 nets.
